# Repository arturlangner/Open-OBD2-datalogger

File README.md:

# Open OBD2 datalogger
This is an OBD2 datalogger running on an NXP Kinetis E that stores engine data and GPS position to an SD card. It supports CAN and K-line protocols. Visualization is done with HTML5 and JavaScript.

# More information

 - [Project description](https://lb9mg.no/2018/02/25/open-obd-datalogger/)
 - [How to implement OBD2 over CAN](https://lb9mg.no/2017/12/27/reading-obd2-data-without-elm327-part-1-can/)
 - [How to implement OBD2 over K-line](https://lb9mg.no/2018/01/02/reading-obd2-data-without-elm327-part-2-k-line/)

 Contact me if you would like a commercial license.

# Hardware

# Demo log

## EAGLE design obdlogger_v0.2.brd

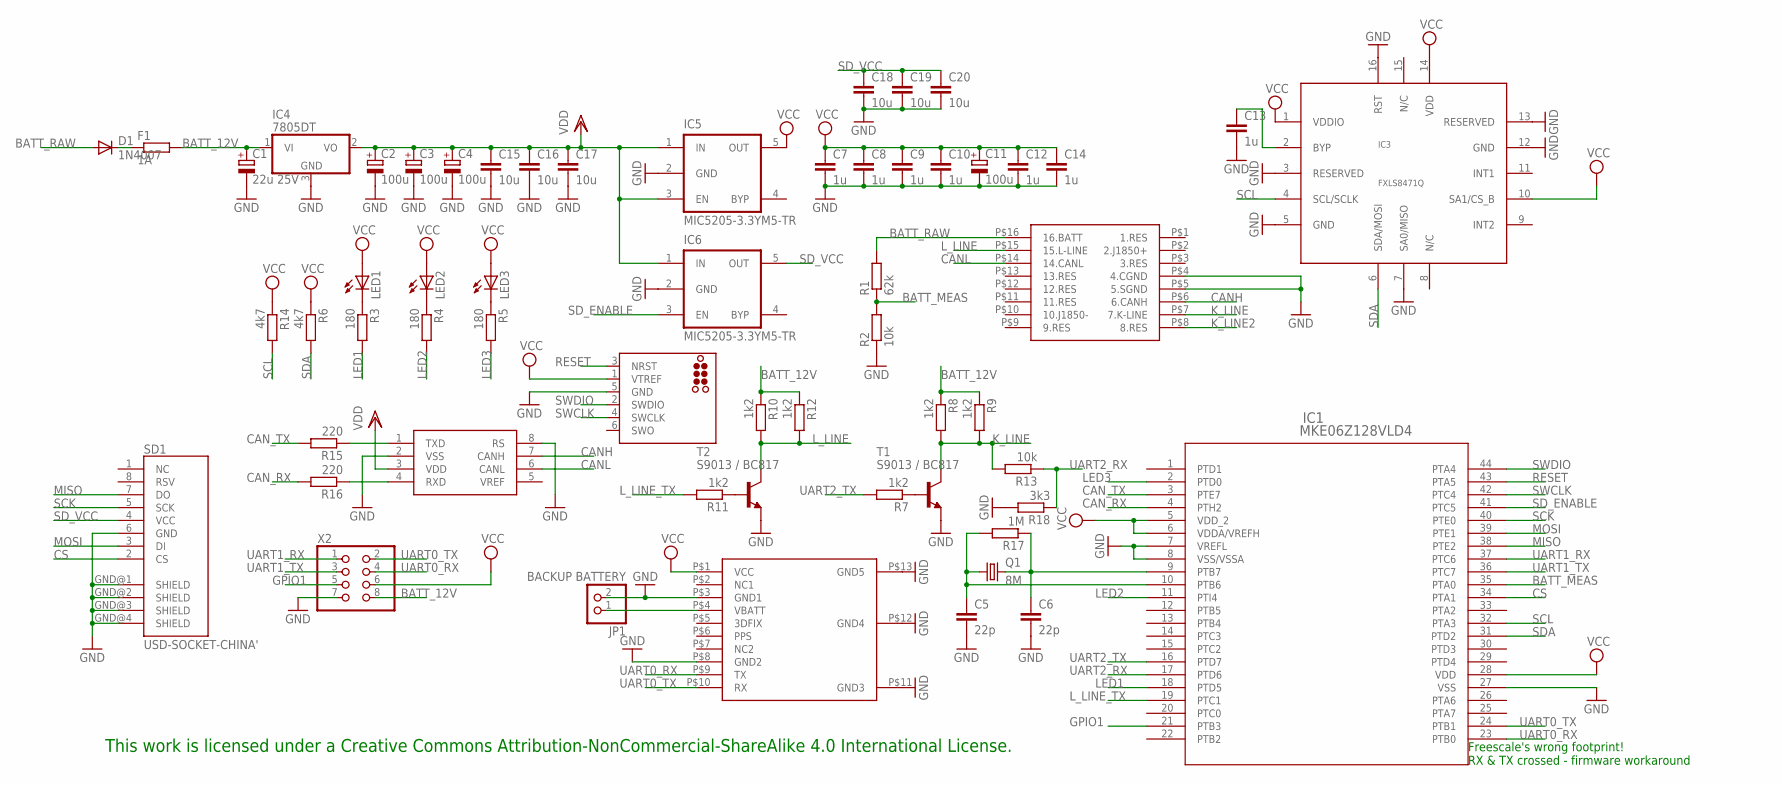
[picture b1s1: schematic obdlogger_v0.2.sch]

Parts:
C1: 22u 25V; SMC_C
C2, C3, C4, C11: 100u; SMC_B
C5, C6: 22p; C0603K
C7, C8, C9, C10, C12, C13, C14: 1u; C0603K
C15, C16, C17, C18, C19, C20: 10u; C0603K
D1: 1N4007; C1702-05
F1: 1A; R1206
IC1: MKE06Z128VLD4; LQFP-44_10X10X1.4
IC2: MCP2561; SO08
IC3: FXLS8471Q; 16QFN-5/3
IC4: 7805DT; TO252
IC5, IC6: MIC5205-3.3YM5-TR; SOT-23-5
JP1: BACKUP BATTERY; 1X02
LED1, LED2, LED3: LED3MM
Q1: 8M; HC49UP
R1: 62k; R0603
R2, R13: 10k; R0603
R3, R4, R5: 180; R0603
R6, R14: 4k7; R0603
R7, R11: 1k2; R0603
R8, R9, R10, R12: 1k2; M1206
R15, R16: 220; R0603
R17: 1M; R0603
R18: 3k3; R0603
SD1: USD-SOCKET-CHINA'; USD-SOCKET-PP
T1, T2: S9013 / BC817; SOT23-BEC
U$2: SWD-NEEDLE; TC2030-MCP
U$4: PA6C
X1: OBD2-RIGHT-ANGLEPROPER; OBD2-RIGHT-ANGLE-PCB-PROPER
X2: PINHD-2X4; 2X04

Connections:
BATT_12V: C1.+, F1.2, IC4.1 (VI), R8.1, R9.1, R10.1, R12.1, X2.8
BATT_MEAS: IC1.35 (PTA0), R1.1, R2.2
BATT_RAW: D1.A, R1.2, X1.P$16 (16.BATT)
CANH: IC2.7 (CANH), X1.P$6 (6.CANH)
CANL: IC2.6 (CANL), X1.P$14 (14.CANL)
CAN_RX: IC1.4 (PTH2), R16.2
CAN_TX: IC1.3 (PTE7), R15.2
CS: IC1.34 (PTA1), SD1.2 (CS)
GND: C1.-, C2.-, C3.-, C4.-, C5.2, C6.2, C7.2, C8.2, C9.2, C10.2, C11.-, C12.2, C13.2, C14.2, C15.2, C16.2, C17.2, C18.2, C19.2, C20.2, IC1.7 (VREFL), IC1.8 (VSS/VSSA), IC1.27 (VSS), IC2.2 (VSS), IC2.8 (RS), IC3.3 (RESERVED), IC3.5 (GND), IC3.7 (SA0/MISO), IC3.12 (GND), IC3.13 (RESERVED), IC3.16 (RST), IC4.3 (GND), IC5.2 (GND), IC6.2 (GND), JP1.2, R2.1, R18.2, SD1.6 (GND), SD1.GND@1 (SHIELD), SD1.GND@2 (SHIELD), SD1.GND@3 (SHIELD), SD1.GND@4 (SHIELD), T1.E, T2.E, U$2.5 (GND), U$4.P$3 (GND1), U$4.P$8 (GND2), U$4.P$11 (GND3), U$4.P$12 (GND4), U$4.P$13 (GND5), X1.P$4 (4.CGND), X1.P$5 (5.SGND), X2.7
GPIO1: IC1.21 (PTB3), X2.5
K_LINE: R8.2, R9.2, R13.2, T1.C, X1.P$7 (7.K-LINE)
K_LINE2: X1.P$8 (8.RES)
LED1: IC1.18 (PTD5), R3.2
LED2: IC1.11 (PTI4), R4.2
LED3: IC1.2 (PTD0), R5.2
L_LINE: R10.2, R12.2, T2.C, X1.P$15 (15.L-LINE)
L_LINE_TX: IC1.19 (PTC1), R11.2
MISO: IC1.38 (PTE2), SD1.7 (DO)
MOSI: IC1.39 (PTE1), SD1.3 (DI)
unnamed: LED1.K (C), R3.1
unnamed: JP1.1, U$4.P$4 (VBATT)
unnamed: R7.1, T1.B
unnamed: LED2.K (C), R4.1
unnamed: LED3.K (C), R5.1
unnamed: C6.1, IC1.9 (PTB7), Q1.2, R17.1
unnamed: C5.1, IC1.10 (PTB6), Q1.1, R17.2
unnamed: C13.1, IC3.2 (BYP)
unnamed: IC2.1 (TXD), R15.1
unnamed: IC2.4 (RXD), R16.1
unnamed: D1.C, F1.1
unnamed: R11.1, T2.B
RESET: IC1.43 (PTA5), U$2.3 (NRST)
SCK: IC1.40 (PTE0), SD1.5 (SCK)
SCL: IC1.32 (PTA3), IC3.4 (SCL/SCLK), R14.2
SDA: IC1.31 (PTD2), IC3.6 (SDA/MOSI), R6.2
SD_ENABLE: IC1.41 (PTC5), IC6.3 (EN)
SD_VCC: C18.1, C19.1, C20.1, IC6.5 (OUT), SD1.4 (VCC)
SWCLK: IC1.42 (PTC4), U$2.4 (SWCLK)
SWDIO: IC1.44 (PTA4), U$2.2 (SWDIO)
UART0_RX: IC1.23 (PTB0), U$4.P$9 (TX), X2.4
UART0_TX: IC1.24 (PTB1), U$4.P$10 (RX), X2.2
UART1_RX: IC1.37 (PTC6), X2.1
UART1_TX: IC1.36 (PTC7), X2.3
UART2_RX: IC1.17 (PTD6), R13.1, R18.1
UART2_TX: IC1.16 (PTD7), R7.2
VCC: C7.1, C8.1, C9.1, C10.1, C11.+, C12.1, C14.1, IC1.5 (VDD_2), IC1.6 (VDDA/VREFH), IC1.28 (VDD), IC3.1 (VDDIO), IC3.10 (SA1/CS_B), IC3.14 (VDD), IC5.5 (OUT), LED1.A, LED2.A, LED3.A, R6.1, R14.1, U$2.1 (VTREF), U$4.P$1 (VCC), X2.6
VCC_5V: C2.+, C3.+, C4.+, C15.1, C16.1, C17.1, IC2.3 (VDD), IC4.2 (VO), IC5.1 (IN), IC5.3 (EN), IC6.1 (IN)

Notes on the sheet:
Freescale's wrong footprint! RX & TX crossed - firmware workaround
This work is licensed under a Creative Commons Attribution-NonCommercial-ShareAlike 4.0 International License.

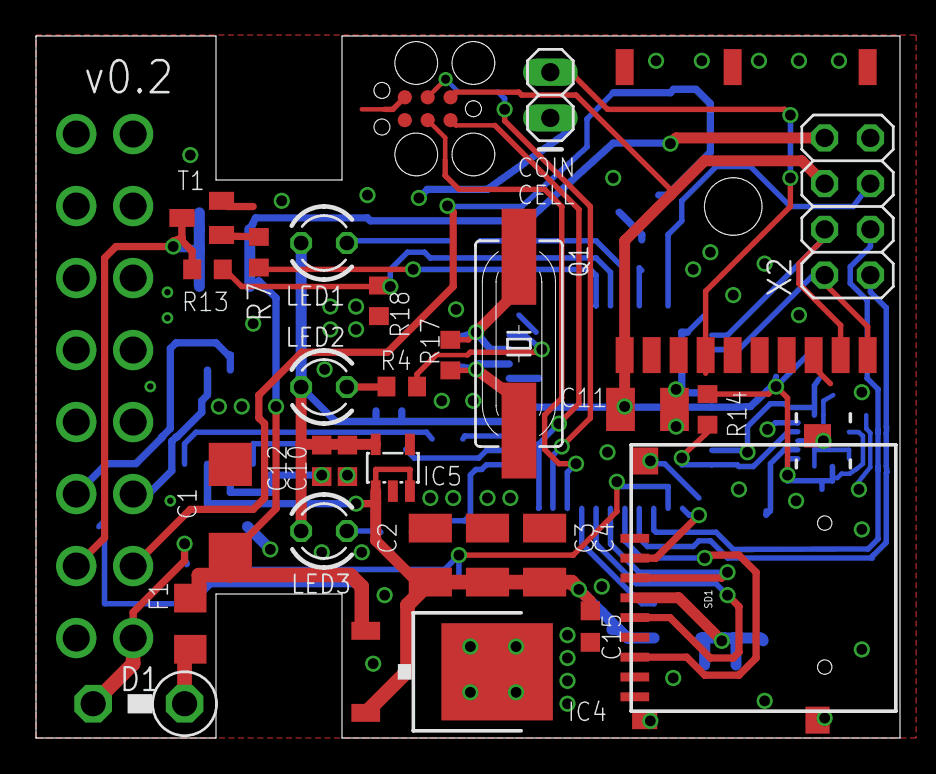
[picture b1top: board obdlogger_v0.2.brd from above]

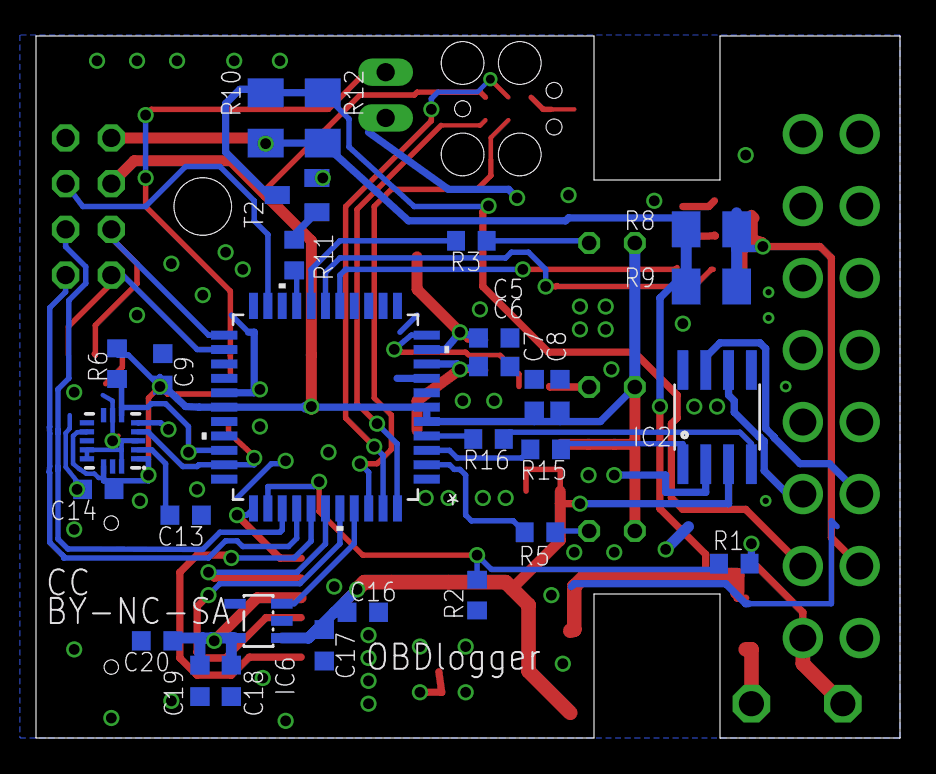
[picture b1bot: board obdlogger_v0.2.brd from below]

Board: 2 copper layers, 48.0 x 39.0 mm, 58 parts (29 on the bottom side), 46 nets.

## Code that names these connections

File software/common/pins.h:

#pragma once
#include <MKE06Z4.h>

#ifdef BOARD_EVK

#define LED_INIT() do {\
		GPIOB_PDDR |= PORT_PUE1_PTGPE5_MASK | PORT_PUE1_PTGPE6_MASK | PORT_PUE1_PTGPE7_MASK;/*set as outputs*/\
		GPIOB_PSOR = PORT_PUE1_PTGPE5_MASK | PORT_PUE1_PTGPE6_MASK | PORT_PUE1_PTGPE7_MASK;/*all leds off*/\
		} while (0)

#define LED1_ON()    GPIOB_PCOR = PORT_PUE1_PTGPE5_MASK
#define LED1_OFF()   GPIOB_PSOR = PORT_PUE1_PTGPE5_MASK
#define LED2_ON()  GPIOB_PCOR = PORT_PUE1_PTGPE6_MASK
#define LED2_OFF() GPIOB_PSOR = PORT_PUE1_PTGPE6_MASK
#define LED3_ON()   GPIOB_PCOR = PORT_PUE1_PTGPE7_MASK
#define LED3_OFF()  GPIOB_PSOR = PORT_PUE1_PTGPE7_MASK

#define SPI0_PINS_INIT() do { \
		GPIOB_PDDR |= PORT_PUE1_PTEPE3_MASK; /*PTE3 is CS GPIO*/ \
		SIM_PINSEL0 |= SIM_PINSEL_SPI0PS_MASK; /*map pins: SCK PTE0, MOSI PTE1, MISO PTE2*/ \
		} while (0)

#define SPI0_CS_HIGH()  GPIOB_PSOR = PORT_PUE1_PTEPE3_MASK
#define SPI0_CS_LOW()   GPIOB_PCOR = PORT_PUE1_PTEPE3_MASK

#define SD_POWER_ON() //not used by the development kit, card is always on
#define SD_POWER_OFF()
#warning "Build uses EVK pins!!!"
#else
//LED1 PTD5
//LED2 PTI4
//LED3 PTD0
#define LED_INIT() do {\
		GPIOA_PDDR |= PORT_PUE0_PTDPE5_MASK/*LED1*/ | PORT_PUE0_PTDPE0_MASK/*LED3*/ ; /*set as outputs*/\
		GPIOA_PSOR = PORT_PUE0_PTDPE5_MASK/*LED1*/ | PORT_PUE0_PTDPE0_MASK/*LED3*/ ; /*all leds off*/\
		GPIOC_PDDR |= PORT_PUE2_PTIPE4_MASK/*LED2*/ ; /*set as outputs*/\
		GPIOC_PSOR = PORT_PUE2_PTIPE4_MASK/*LED2*/ ; /*all leds off*/\
		} while (0)

#define LED1_ON()    GPIOA_PCOR = PORT_PUE0_PTDPE5_MASK
#define LED1_OFF()   GPIOA_PSOR = PORT_PUE0_PTDPE5_MASK
#define LED2_ON()  GPIOC_PCOR = PORT_PUE2_PTIPE4_MASK
#define LED2_OFF() GPIOC_PSOR = PORT_PUE2_PTIPE4_MASK
#define LED3_ON()   GPIOA_PCOR = PORT_PUE0_PTDPE0_MASK
#define LED3_OFF()  GPIOA_PSOR = PORT_PUE0_PTDPE0_MASK

#define SPI0_PINS_INIT() do { \
		GPIOA_PDDR |= PORT_PUE0_PTAPE1_MASK; /*PTA1 is CS GPIO*/ \
		GPIOA_PSOR = PORT_PUE0_PTAPE1_MASK; /*CS HIGH*/ \
		SIM_PINSEL0 |= SIM_PINSEL_SPI0PS_MASK; /*map pins: SCK PTE0, MOSI PTE1, MISO PTE2*/ \
		} while (0)

#define SPI0_PINS_DEINIT() do { /*all pins GPIO - low to reduce power consumption*/ \
		GPIOA_PDDR |= PORT_PUE0_PTAPE1_MASK; /*PTA1 is CS GPIO*/ \
		GPIOA_PCOR = PORT_PUE0_PTAPE1_MASK; /*CS HIGH*/ \
		GPIOB_PDDR |= PORT_PUE1_PTEPE0_MASK | PORT_PUE1_PTEPE1_MASK | PORT_PUE1_PTEPE2_MASK; /*SCK, MOSI, MISO*/ \
		GPIOB_PCOR |= PORT_PUE1_PTEPE0_MASK | PORT_PUE1_PTEPE1_MASK | PORT_PUE1_PTEPE2_MASK; /*all low*/ \
		} while (0)

#define SPI0_CS_HIGH()  GPIOA_PSOR = PORT_PUE0_PTAPE1_MASK
#define SPI0_CS_LOW()   GPIOA_PCOR = PORT_PUE0_PTAPE1_MASK

#define SD_POWER_ON() do { \
		GPIOA_PDDR |= PORT_PUE0_PTCPE5_MASK; /*PTC5 is LDO enable line*/ \
		GPIOA_PSOR = PORT_PUE0_PTCPE5_MASK; /*line high, enable LDO*/ \
		PORT_PUE1 = PORT_PUE1_PTEPE2_MASK; /*MISO pullup*/ \
		PORT_PUE0 = PORT_PUE0_PTAPE1_MASK; /*CS pullup*/ \
		} while (0)

#define SD_POWER_OFF() GPIOA_PCOR |= PORT_PUE0_PTCPE5_MASK /*line low, disable LDO*/


#define K_LINE_LOW()  GPIOA_PSOR = PORT_PUE0_PTDPE7_MASK //line drives NPN transistor so GPIO high is K-Line low
#define K_LINE_HIGH() GPIOA_PCOR = PORT_PUE0_PTDPE7_MASK //line drives NPN transistor so GPIO low is K-Line high

#define K_LINE_INIT() do { \
		GPIOA_PDDR |= PORT_PUE0_PTDPE7_MASK/*K-Line TX - output*/; \
		K_LINE_HIGH(); \
		} while (0)

#define K_LINE_UART UART2
#define K_LINE_UART_IRQ_HANDLER UART2_IRQHandler
#define K_LINE_UART_IRQn UART2_IRQn
#define K_LINE_UART_CLOCK_ENABLE_MASK SIM_SCGC_UART2_MASK

#define L_LINE_INIT() do { \
		GPIOA_PDDR |= PORT_PUE0_PTCPE1_MASK/*L-Line - output*/; \
		L_LINE_HIGH(); \
		} while (0)

#define L_LINE_LOW()  GPIOA_PSOR = PORT_PUE0_PTCPE1_MASK //line drives NPN transistor so GPIO high is L-Line low
#define L_LINE_HIGH() GPIOA_PCOR = PORT_PUE0_PTCPE1_MASK //line drives NPN transistor so GPIO low is L-Line high

#define UART_BITBANG_TX_INIT() do { \
		GPIOA_PDDR |= PORT_PUE0_PTBPE0_MASK/*PTB0*/; \
		UART_BITBANG_TX_HIGH(); \
		} while (0)

#define UART_BITBANG_TX_HIGH() GPIOA_PSOR = PORT_PUE0_PTBPE0_MASK
#define UART_BITBANG_TX_LOW() GPIOA_PCOR = PORT_PUE0_PTBPE0_MASK

#endif

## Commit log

2018-02-25 Grammar fix
2018-02-25 Create LICENSE
    Adds license

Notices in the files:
parts and their libraries:
SparkFun: Licensing: CC v3.0 Share-Alike You are welcome to use this library for commercial purposes.
tag-connect: ©2009 ROFA.cz - modified and updated by Robert Darlington ‹rdarlington@gmail.com›
